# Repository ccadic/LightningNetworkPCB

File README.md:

# LightningNetworkPCB
This is a lightning network esp32S2 experimentation PCB (POS/ATM)

Licence is GPL3 I never read :) But philosophy is: do what you want with it. 
If you want to encourage me, here is my BTC wallet address: bc1qdy8alfz6t623trqzk2m0mzrz8w87wwgjc9azgc
My LN Wallet: lnbc1p38nqhcpp5dr46a44fh3jh4uhenvvuxhza30jzzg2auevfjff3hw0uxne34k8qdqu2askcmr9wssx7e3q2dshgmmndp5scqzpgxqyz5vqsp5hzff9unn0vs4f9qsam9a67ffl5hydvs7n4yxd2n6f3aa29qd9jks9qyyssq4y6nllz8ku0qk05glep3g6frwyypptjahnv4t9neszszl07pl944seglzcfk7q9hreuq62wl3f8jjn4ugytncnhhm3zngr34ektzegspkv3cxk

This board is using
An ESP32-S2 wroom chip from espressif
A 2.8 inch touch screen (ILI9341 SPI)
A 3x4 keypad (https://www.amazon.fr/gp/product/B07GFDKJYZ/ref=ppx_yo_dt_b_asin_title_o08_s00?ie=UTF8&th=1)

The board is equiped with a USB-C plug to bring 5V and to upload ESP32S2 scketches
The board also has a 12v regulator thru a barrel jack, should you want to connect a 12v source and fee the coin selector with 12v.  The 12v si also converted to 3.3v for the ESP32 to run.

You have a connector for the CH-926 Coin selector. Have a look at the PCB writing (the wiring is explained)
The CH-926 coin pin is 5V. I built a level shifter to be able to talk to the ESP32 pin in 3.3v

You also have a bunch of extra GPIO / SPI and I2C connector on the top back of the PCB. It allows you to connect a TTL thermal printer, should you want to create a LN-POS
You also have extra ESP32-S TRX1 TRX0 pins to talk to another devive thru UART. I have added these to be able to talk to a CAM-ESP32, should you want to read QR code from another ESP32 device
You hace I2C SDA/SCL pins to connect, for instance, a NFC reader/writer to process payments.

Have fun

Dr Philippe CADIC
pcadic(at)gmail.com

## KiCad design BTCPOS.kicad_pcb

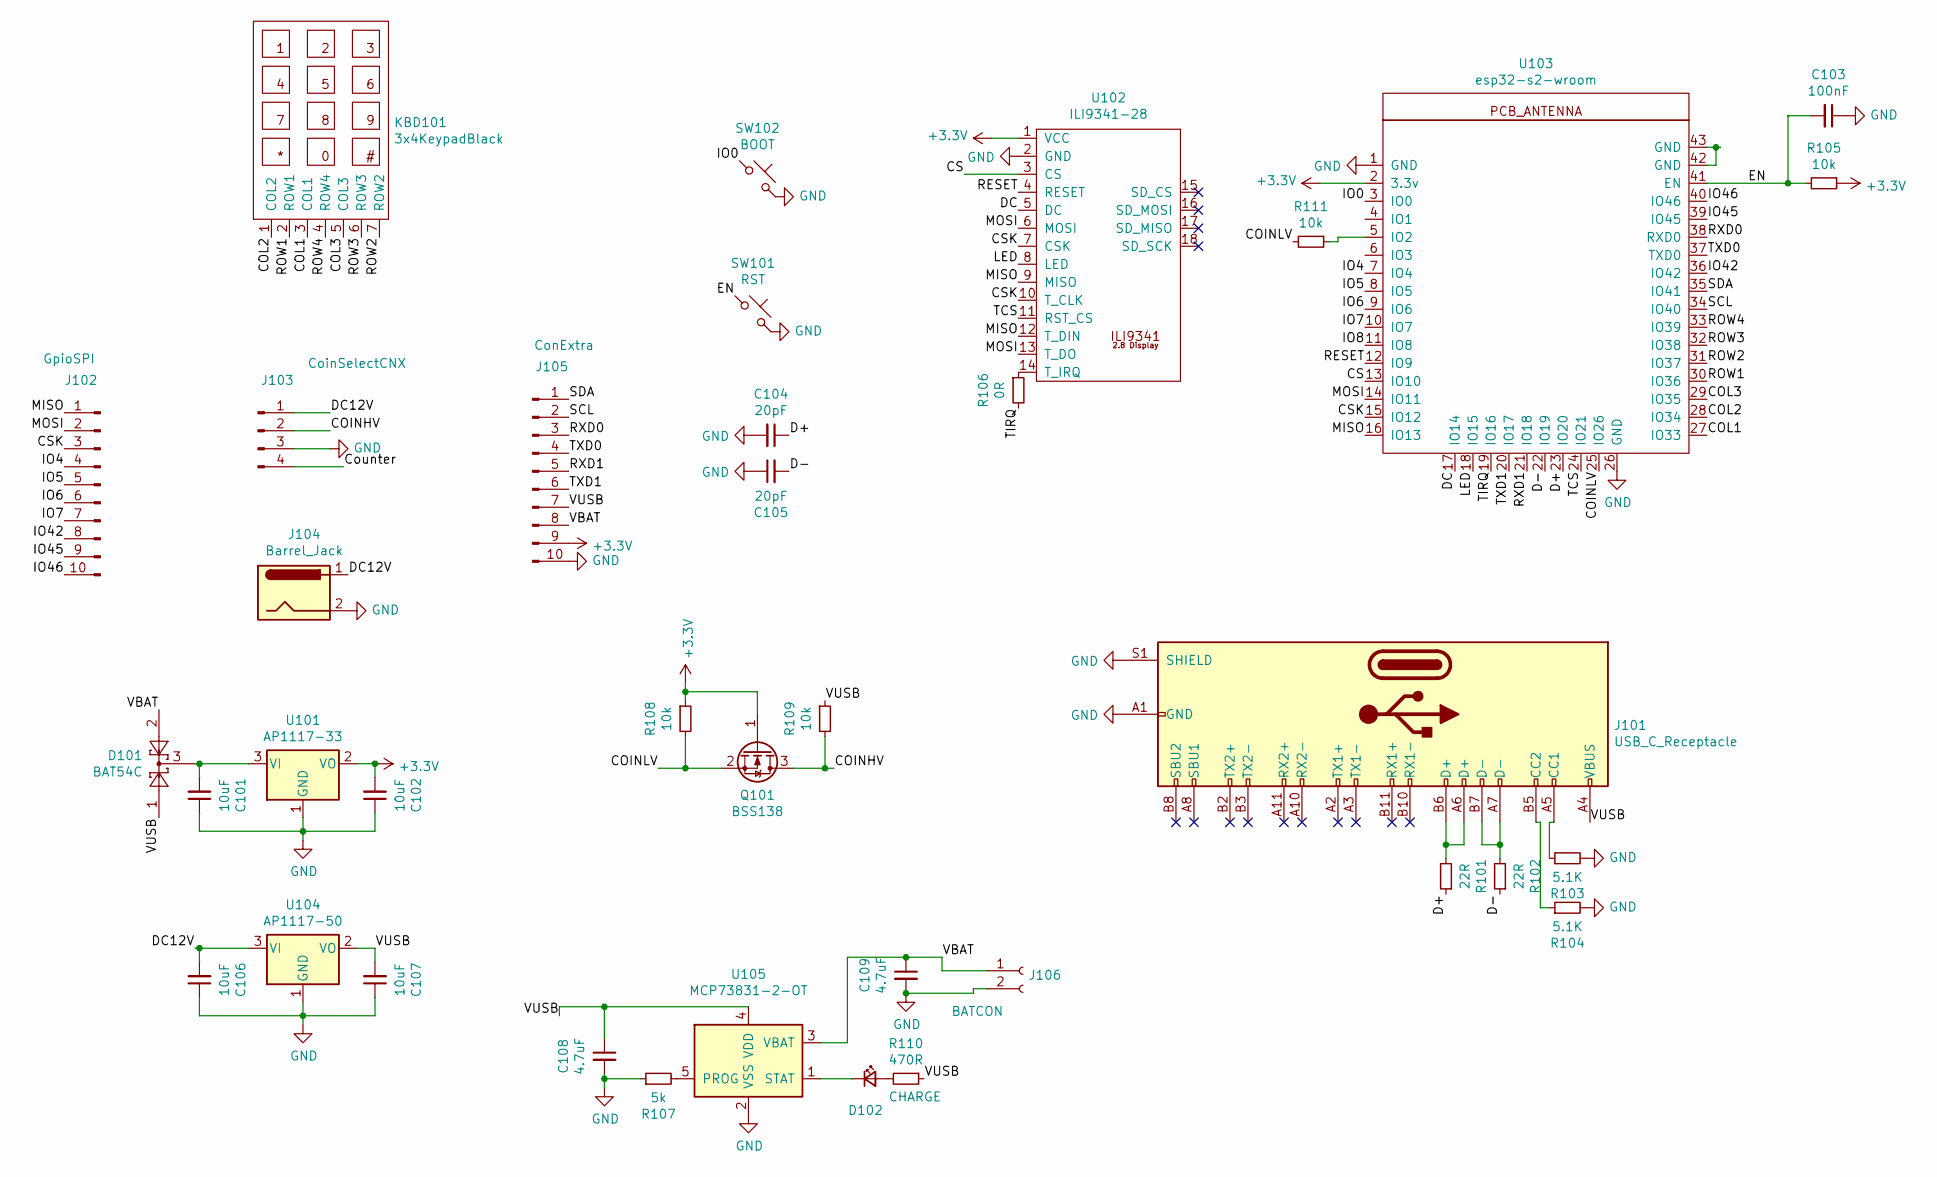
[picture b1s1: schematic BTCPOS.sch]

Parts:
C101, C102, C106, C107: 10uF; C_0805_2012Metric_Pad1.18x1.45mm_HandSolder
C103: 100nF; C_0805_2012Metric_Pad1.18x1.45mm_HandSolder
C104, C105: 20pF; C_0805_2012Metric_Pad1.18x1.45mm_HandSolder
C108, C109: 4.7uF; C_0805_2012Metric_Pad1.18x1.45mm_HandSolder
D101: BAT54C; SOT-23
D102: CHARGE; LED_0805_2012Metric_Pad1.15x1.40mm_HandSolder
J101: USB_C_Receptacle; GT-USB-7010
J102: GpioSPI; PinSocket_1x10_P2.54mm_Vertical
J103: CoinSelectCNX; TerminalBlock_bornier-4_P5.08mm
J104: Barrel_Jack; BARREL_JACK
J105: ConExtra; PinSocket_1x10_P2.54mm_Vertical
J106: BATCON; JST_PH_S2B-PH-SM4-TB_1x02-1MP_P2.00mm_Horizontal
KBD101: 3x4KeypadBlack; KeyPad_3x4
Q101: BSS138; SOT-23
R101, R102: 22R; R_0805_2012Metric_Pad1.20x1.40mm_HandSolder
R103, R104: 5.1K; R_0805_2012Metric_Pad1.20x1.40mm_HandSolder
R105, R108, R109, R111: 10k; R_0805_2012Metric_Pad1.20x1.40mm_HandSolder
R106: 0R; R_0805_2012Metric_Pad1.20x1.40mm_HandSolder
R107: 5k; R_0805_2012Metric_Pad1.20x1.40mm_HandSolder
R110: 470R; R_0805_2012Metric_Pad1.20x1.40mm_HandSolder
SW101: RST; SKRPABE010
SW102: BOOT; SKRPABE010
U101: AP1117-33; SOT-223-3_TabPin2
U102: ILI9341-28; ILI9341-2_8-noSD
U103: esp32-s2-wroom; esp32-s2-wrooom
U104: AP1117-50; SOT-223-3_TabPin2
U105: MCP73831-2-OT; SOT-23-5

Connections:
+3V3: C102.2, J105.9, Q101.1 (G), R105.1, R108.1, U101.2 (VO), U102.1 (VCC), U103.2 (3.3v)
/COINHV: J103.2, Q101.3 (D), R109.2
/COINLV: Q101.2 (S), R108.2, R111.2, U103.25 (IO26)
/COL1: KBD101.3 (COL1), U103.27 (IO33)
/COL2: KBD101.1 (COL2), U103.28 (IO34)
/COL3: KBD101.5 (COL3), U103.29 (IO35)
/CS: U102.3 (CS), U103.13 (IO10)
/CSK: J102.3, U102.7 (CSK), U102.10 (T_CLK), U103.15 (IO12)
/D+: C104.1, R101.1, U103.23 (IO20)
/D-: C105.2, R102.1, U103.22 (IO19)
/DC: U102.5 (DC), U103.17 (IO14)
/DC12V: C106.2, J103.1, J104.1, U104.3 (VI)
/EN: C103.2, R105.2, SW101.1, U103.41 (EN)
/IO0: SW102.1, U103.3 (IO0)
/IO4: J102.4, U103.7 (IO4)
/IO5: J102.5, U103.8 (IO5)
/IO6: J102.6, U103.9 (IO6)
/IO7: J102.7, U103.10 (IO7)
/IO42: J102.8, U103.36 (IO42)
/IO45: J102.9, U103.39 (IO45)
/IO46: J102.10, U103.40 (IO46)
/LED: U102.8 (LED), U103.18 (IO15)
/MISO: J102.1, U102.9 (MISO), U102.12 (T_DIN), U103.16 (IO13)
/MOSI: J102.2, U102.6 (MOSI), U102.13 (T_DO), U103.14 (IO11)
/RESET: U102.4 (RESET), U103.12 (IO9)
/ROW1: KBD101.2 (ROW1), U103.30 (IO36)
/ROW2: KBD101.7 (ROW2), U103.31 (IO37)
/ROW3: KBD101.6 (ROW3), U103.32 (IO38)
/ROW4: KBD101.4 (ROW4), U103.33 (IO39)
/RXD0: J105.3, U103.38 (RXD0)
/RXD1: J105.5, U103.21 (IO18)
/SCL: J105.2, U103.34 (IO40)
/SDA: J105.1, U103.35 (IO41)
/TCS: U102.11 (RST_CS), U103.24 (IO21)
/TIRQ: R106.2, U103.19 (IO16)
/TXD0: J105.4, U103.37 (TXD0)
/TXD1: J105.6, U103.20 (IO17)
/VBAT: C109.1, D101.2, J105.8, J106.1, U105.3 (VBAT)
/VUSB: C107.2, C108.1, D101.1, J101.A4 (VBUS), J101.A9 (VBUS), J101.B4 (VBUS), J101.B9 (VBUS), J105.7, R109.1, R110.1, U104.2 (VO), U105.4 (VDD)
GND: C101.1, C102.1, C103.1, C104.2, C105.1, C106.1, C107.1, C108.2, C109.2, J101.A1 (GND), J101.A12 (GND), J101.B1 (GND), J101.B12 (GND), J101.S1 (SHIELD), J103.3, J104.2, J105.10, J106.2, R103.2, R104.2, R107.1, SW101.2, SW102.2, U101.1 (GND), U102.2 (GND), U103.1 (GND), U103.26 (GND), U104.1 (GND), U105.2 (VSS)
unnamed: C101.2, D101.3, U101.3 (VI)
unnamed: D102.1 (K), U105.1 (STAT)
unnamed: D102.2 (A), R110.2
unnamed: J101.A5 (CC1), R103.1
unnamed: J101.A6 (D+), J101.B6 (D+), R101.2
unnamed: J101.A7 (D-), J101.B7 (D-), R102.2
unnamed: J101.B5 (CC2), R104.1
unnamed: R106.1, U102.14 (T_IRQ)
unnamed: R107.2, U105.5 (PROG)
unnamed: R111.1, U103.5 (IO2)
unnamed: U103.42 (GND), U103.43 (GND)

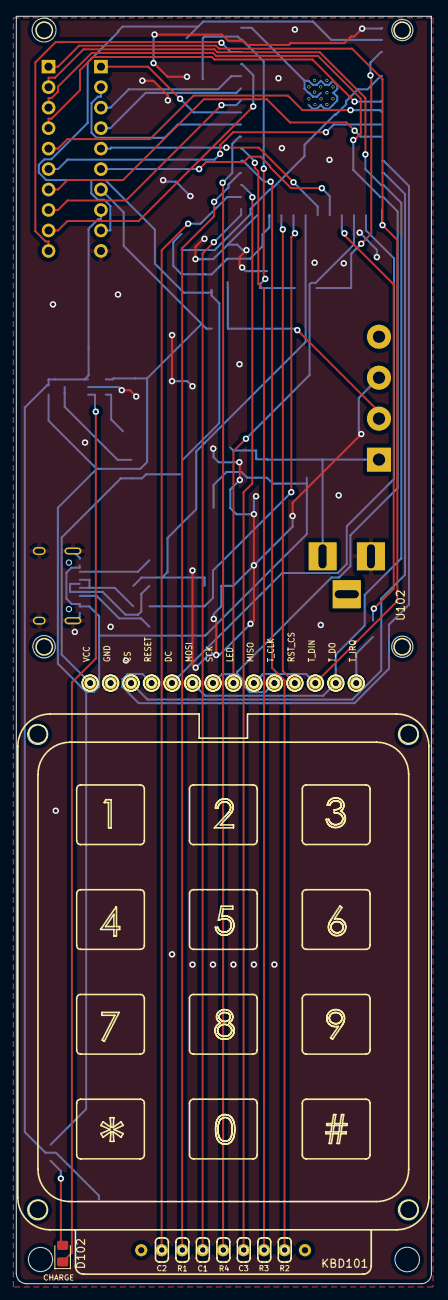
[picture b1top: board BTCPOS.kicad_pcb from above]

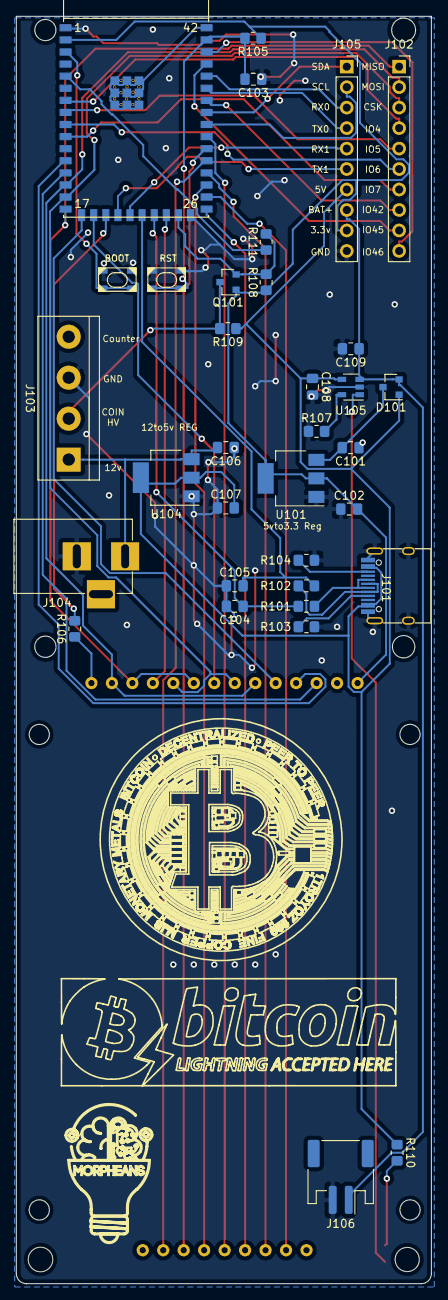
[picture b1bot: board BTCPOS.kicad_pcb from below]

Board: 2 copper layers, 51.5 x 157.2 mm, 38 parts (35 on the bottom side), 51 nets.

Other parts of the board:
REF10: BTC6
